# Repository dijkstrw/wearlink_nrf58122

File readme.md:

# Wearlink v2

## Introduction

While looking for a new winter coat I stumbled on a Taiwanese manufacturer
selling a black and blue winter coat with keys on the sleeve.

The keys legend betray their intended purpose: volume control, play/pause and
forward/reverse. I listen to podcasts on my android phone in the car and on the
bike, and this would make a great way to control those even when wearing
gloves!

It turns out that the real keypad is glued to the inside of the sleeve, just
under the outer coat layers. A ruggedized two-wire cable connected the keypad
to a 2.5mm TRS in the left chest pocket.

The keypad is manufactured by [FibreTronic](http://fibretronic.com) under the
moniker connectedwear. They sell a range of keypads (my coat has the
[KP2-5SH](http://fibretronic.com/connectedwear/KP25SH) ) and a range of
controllers that can be connected to the keypad. Naturally none of their
controllers work for me. A couple of years I built my
[first controller](https://github.com/dijkstrw/wearlink), and this project is
an update of that design with these requirements:

* No wiring between controller and phone. Making reliable connections between
  flexible wire and hard connectors is a hard problem. I have had to replace
  the connections many times, and have not found a good way to make them last
  years when wires can flex due to walking.

* No wiring means internal battery -- be frugal in power consumption.

* Default interface to the phone. Ideally no programming on the phone, because
  this somewhat guarantees project longevity.

## My design

A controller that pretends to be a usb keyboard and emits multimedia keys for
keypresses. Bluetooth is used to eliminate wires, and the mcu and pcb has been
designed for low power operation to make that battery go for months. I had
heard good things about Nordic, and went with the
[nRF51822](https://www.nordicsemi.com/eng/Products/Bluetooth-low-energy/nRF51822)
because:

* ARM Cortex M0

* Bluetooth Low Energy

* 128k flash at entry level (but read on)

* Onboard regulators, with a supply range between 1.8 and 3.6V

* JTAG programming using a four wire interface

### nRF51822

BLE is implemented using a soft-core that lives in the first half of the
flash. Your application configures the soft-core structures to get the type of
BLE interface you want, and the soft-core will call event-handlers to indicate
radio or hardware events.

The nRF51822 needs an antenna and careful layout. There are also ready made
boards that can be used as complete dropin modules, we use the S4AT here.

### ADC configuration / wakeup

Fibretronics wearlink is a string of push button (no) switches individually in
series with a resistor. When no button is pressed it is open circuit. When one
button is pressed, the resistance corresponding to that key is present between
the two feed wires.

Running the ADC will cause it to sample. Sampling looks like an input impedance
of ~390k, so to spare the battery the ADC needs to run only when BLE is
active. Q1 is used to make nice detectable falling edges at keypress to ensure
wakeup when not in a BLE conversation.

As the battery discharges our ADC input voltage will drop also. This is
compensated for by periodically measuring the battery voltage and taking that
into account when determining keys pressed.

Note that a TagConnect header is used for JTAG.

### BLE bonding

BLE pairing is stored in flash and reused at next bootup. To make the
controller forget all pairings press key combination PLAY, PLAY, PLAY, VOLUME
DOWN, VOLUME DOWN, VOLUME UP, VOLUME UP directly after controller wakeup.

## Directory structure

* `config` - board configuration files that define clock and peripheral
  configuration for the nrf51. Also the place where the linker file lives

* `doc` - pdf repository for used boards and ics

* `nrf51_sdk_10_0_0` - Download the [SDK](https://developer.nordicsemi.com/nRF5_SDK/nRF51_SDK_v10.x.x/nRF51_SDK_10.0.0_dc26b5e.zip) from Nordic and unzip here

* `schematic` - board schematic and pcb in Kicad

## Next time

* Current nRF51 carrier (S4AT) does not have a LXFT, so even more power can be saved
  next time by choosing or designing a board that does.

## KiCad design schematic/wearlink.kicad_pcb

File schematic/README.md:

WT51822-0S4AT taken from https://github.com/cyrozap/KiCad

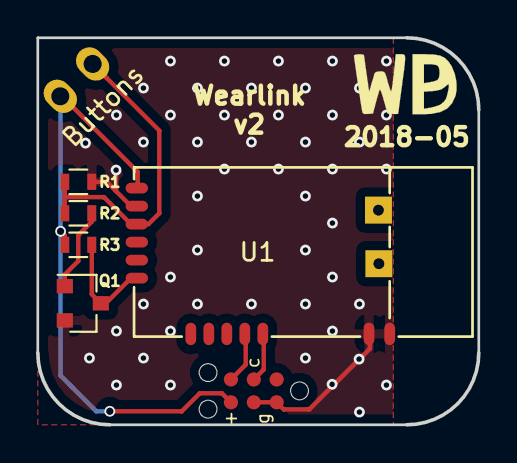
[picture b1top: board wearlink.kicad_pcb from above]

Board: 2 copper layers, 24.5 x 21.5 mm, 8 parts (1 on the bottom side), 7 nets.

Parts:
BT1: Battery 2032; Keystone_3034_1x20mm-CoinCell
Buttons: FibretronicKeypad
J1: JTAG; TC2030-IDC-NL
Q1: MMBT3904; SOT-23
R1: 20k; R_0603
R2, R3: 1M; R_0603
U1: WT51822-0S4AT

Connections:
ADC: Buttons.2, R1.1, R2.2, U1.3
GND: BT1.2, J1.2, J1.4, Q1.2, R1.2, U1.2, U1.12, U1.13
unnamed: J1.3, U1.11
unnamed: J1.5, U1.10
unnamed: Q1.1, R2.1
POWER: BT1.1, Buttons.1, J1.6, R3.1, U1.1
SENSE: Q1.3, R3.2, U1.6

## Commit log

2017-02-10 its work
2017-02-11 Added consumer control
2018-04-07 Using SDK12 example code, trying consumer codes
    Have debugging on usart and a handle howto load via stlink
2018-04-13 cleanup configuration
2018-04-14 After a full erase this works
    So something about renegotiation is broken and needs to be added. Still,
    I have media keys in android, so this is quite cool already.
2018-04-15 Cleanup
2018-04-15 Added initial adc interaction
    ADC reads AIN2 -> P0.1
2018-04-20 Added powerpin for keypad
2018-04-20 gpiote triggered adc reads
2018-04-22 Added first calculations for adc key values
2018-05-03 Tested enable and adc hardware
2018-05-03 Working prototype
    Next step: decrease current draw :)
2018-05-03 Enabled power save, but adc is broken on wakeup
2018-05-04 Now also working after sleep
2018-05-04 Removed sensorsim, added actual battery measurement
2018-05-05 Cleaned up project
    - Removed unnecessary files
    - Added the nrf51 sdk 10.0.0 to make the project timetravel better
2018-05-05 Battery is vcc, cope with adc change @ discharging
    - sample battery quickly after startup to determine current Vdd
    - set ble battery level as a percentage of 3V6
    - remove remaining app buttons
2018-05-05 Started with schematic
2018-05-05 Added footprints, first route
    Seems a little to spacious..
2018-05-06 Auto sleep also when connected but idle
    After n battery measurement intervals with no other actions happening
    also autosleep to save battery.
2018-05-06 Added my measurements
2018-05-06 Cleaned up schematic
    Added holes for module
2018-05-07 Made pcb smaller
2018-05-11 Verified hole sizes WT51822, more pcb cleanup
2018-05-11 Added via stitching
2018-05-13 Removed bsp button interaction, added combos
    When no ble connection is active, the device will look for
    keycombos. Only one is defined at this time, and that item will drop all
    known peers in the device manager, breaking active peerings.
2018-06-02 Bugfix: now add boot button in main.c
2018-06-02 Add S4AT as a new platform
    Prepare for production installation
2018-06-02 As sent to pcbway 20180517
2018-06-10 Adjust idle timer to 20 mins, add start_key
2018-10-21 Added readme.md
